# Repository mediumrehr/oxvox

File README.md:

# Ox Vox

The Ox Vox is a badge add-on created for the DEF CON 25 503 party and BSides PDX 2018 badges. The Ox Vox replaces the two joysticks on the badge with eight buttons and amplified speaker output.

## How To

### Connecting

Connecting the Ox Vox requires removing the joysticks from the badge. The pinouts are different for the DC25 Badge vs the BSides badge, so a few defines need to be changed depending on which badge you are modifying. Each joysticks uses five GPIOs, which allows for eight button inputs (a full octave), audio out, and an amplifier enable (see [Addition](#additions)).

Below shows how to connect the Ox Vox depending on which badge you're modifying.

#### DEF CON 25 503 Party Badge

#### BSides PDX Badge

### Programming

There are a few methods for programming the BMD-300 (NRF52832) SoC with the Ox Vox firmware via SWD. For this this project, I've been using the [BMD-300 Eval Kit](https://www.digikey.com/product-detail/en/rigado-inc/BMD-300-EVAL/1604-1007-ND/5958042) as a Segger J-Link Debugger as outlined in [this article](https://rigado.zendesk.com/hc/en-us/articles/223486428-How-are-the-BMD-200-and-BMD-300-Series-modules-programmed-). There are many cheap (<$10) J-Link-OB devices available that will likely work just as well, or you can probably use any other SWD device you have laying around.

In order to program the board, you need to break out the SWD interface. This requires soldering four male header pins to the pads shown below (directly below the i2c screen header). Looking at the badge from the back, the pins are SWCLK, SWDIO, 3v3, and GND.

If you're using a J-Link interface, the badge should show mount to your OS when you plug it into your computer. You can then drop the appropriate (DC25 vs BSides) compiled hex file into the mounted folder and the NRF52 will take it from there.

If you want to build from source, follow [this guide](https://www.rigado.com/bmd-300-series-getting-started-guide/?wpdmdl=1810) (starting on page 9) for setting up Keil uVision, the nRF5 SDK, and Segger J-Link. Instead of downloading nRF5 SDK v12, download [nRF5 SDK v13.0.0](https://developer.nordicsemi.com/nRF5_SDK/nRF5_SDK_v13.x.x/) (it's possible this code will work with newer SDKs, but I have not tested with them).

## Hardware

PCB files, designed in Eagle v7.7.0, are included in the Hardware folder. The design features eight momentary-push buttons, a basic smoothing and amplifier circuit, and a .8W speaker. The buttons form a full octave keyboard from C (261.6 Hz) to C (523.3 Hz). The BMD-300 outputs a PWM signal that is smoothed and amplified by the LM4861 amplifier.

## Firmware

To build the project, drop the oxvox foldering into examples->peripheral in the SDK and drop components into the root of the SDK (it fixes a bug in the bsp driver and adds the board definitions to the boards folder). Opening oxvox.uvprojx will open the project in uVision. From there you can build and load the hex file onto the board (either by grabbing the hex file in \_build/ and dropping it onto the mounted JLINK device or by using uVision's load feature). If you're using uVision to load the firmware, make sure it is configured to support whatever SWD programmer you are using; you can configure this under Project->Options for Target->Debug.

## Additions

The Ox Vox amplifier, in combination with the OLED display, were quickly draining fresh batteries, so as proposed by [Scanlime](https://twitter.com/scanlime), I added support in the firmware to connect the shutown pin of the LM4861 to pin xxx of the BMD-300. This allows the amplifier to be turned off when no audio is being played in order to save some power, and so it doesn't compete with the current draw when the display is drawing more white pixels in the default image. In order to do this, the shutdown lead (highlighted below) needs to be desoldered and lifted off the pad, then wired to the xxx pad on the Badge. The shutdown pin was originally connected to ground so the amplifier would remain on, therefore part of the trace is under the LM4861. The easiest way to break that connection is to lift the lead instead of disconnect the pad.

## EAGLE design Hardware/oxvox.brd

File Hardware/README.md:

### OX VOX Hardware
Schematic and layout created using [Eagle 7.7.0](https://www.autodesk.com/products/eagle/overview)

The design features eight momentary-push buttons, a basic smoothing and amplifier circuit, and a 800mW speaker. The buttons form a full octave keyboard from C (261.6 Hz) to C (523.3 Hz). The BMD-300 outputs a PWM signal that is smoothed and amplified by the LM4861 amplifier.

This layout is slightly different from the DC25 and BSidesPDX layouts. It features the LM4861 shutdown pin broken out, as suggested by [Micah Scott](https://github.com/scanlime). By breaking out the shutdown pin and connecting it to the remaining available BMD-300 GPIO, the amplifier can be to shutdown when not in use in order to save power. Please see the connection section for how to connect this, or connect it to ground to keep the amplifier always on.

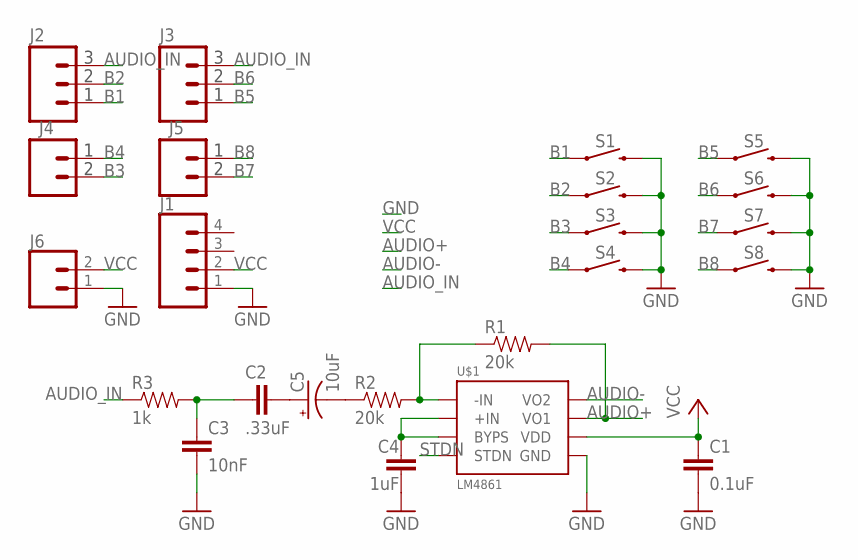
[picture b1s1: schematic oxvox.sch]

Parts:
C1: 0.1uF; 0603-CAP
C2: .33uF; 0603-CAP
C3: 10nF; 0603-CAP
C4: 1uF; 0603-CAP
C5: 10uF; RADIAL_SMT_4MM
J1: CONN_04; 1X04
J2, J3: M03-PTH_LONG_NO_SILK_BOT; M03_LONG_NO_SILK_BOTTOM
J4, J5: M02-PTH_LONG_NO_SILK_BOT; M02_LONG_NO_SILK_BOTTOM
J6: CONN_02; 1X02
R1, R2: 20k; 0805
R3: 1k; 0603-RES
S1, S2, S3, S4, S5, S6, S7, S8: MOMENTARY-SWITCH-SPST-PTH-6.0MM-KIT-ALL2; TACTILE_SWITCH_PTH_6.0MM_KIT_NOSILK
U$1: LM4861; 8-SOIC

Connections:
AUDIO+: R1.2, U$1.P$5 (VO1)
AUDIO-: U$1.P$8 (VO2)
AUDIO_IN: J2.P$3, J3.P$3, R3.1
B1: J2.P$1, S1.1, S1.2 (1)
B2: J2.P$2, S2.1, S2.2 (1)
B3: J4.P$2, S3.1, S3.2 (1)
B4: J4.P$1, S4.1, S4.2 (1)
B5: J3.P$1, S5.1, S5.2 (1)
B6: J3.P$2, S6.1, S6.2 (1)
B7: J5.P$2, S7.1, S7.2 (1)
B8: J5.P$1, S8.1, S8.2 (1)
GND: C1.2, C3.2, C4.2, J1.1, J6.1, S1.3 (2), S1.4 (2), S2.3 (2), S2.4 (2), S3.3 (2), S3.4 (2), S4.3 (2), S4.4 (2), S5.3 (2), S5.4 (2), S6.3 (2), S6.4 (2), S7.3 (2), S7.4 (2), S8.3 (2), S8.4 (2), U$1.P$7 (GND)
unnamed: R1.1, R2.2, U$1.P$4 (-IN)
unnamed: C2.2, C3.1, R3.2
unnamed: C5.P$2 (-), R2.1
unnamed: C4.1, U$1.P$2 (BYPS), U$1.P$3 (+IN)
unnamed: C2.1, C5.P$1 (+)
STDN: U$1.P$1 (STDN)
VCC: C1.1, J1.2, J6.2, U$1.P$6 (VDD)

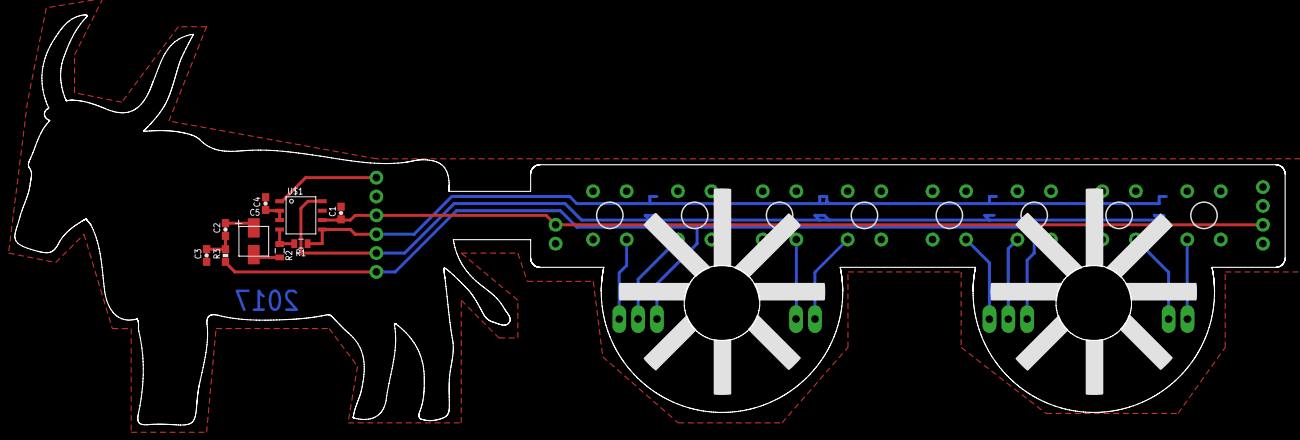
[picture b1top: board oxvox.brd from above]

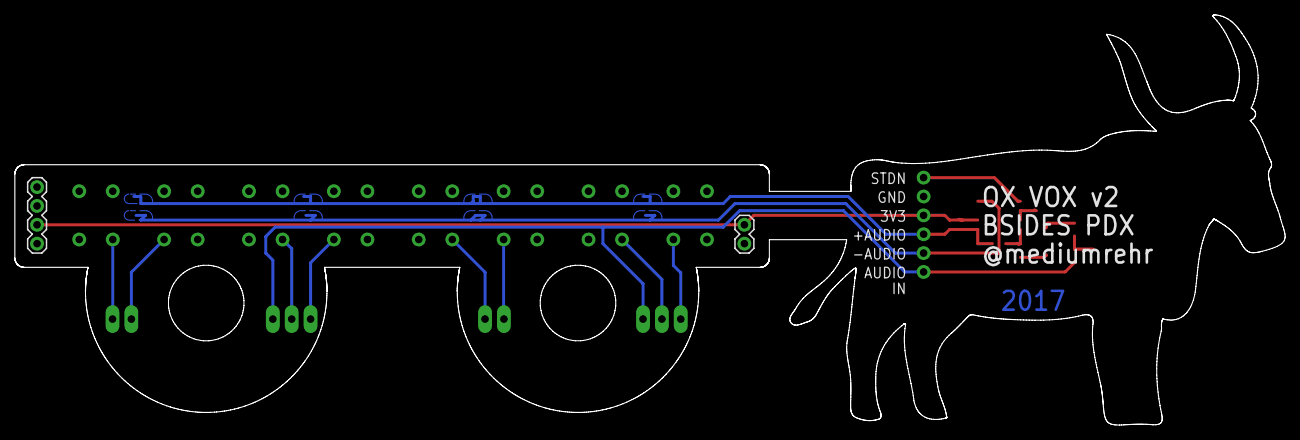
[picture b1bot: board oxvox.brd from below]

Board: 2 copper layers, 171.1 x 55.2 mm, 23 parts (6 on the bottom side), 17 nets.

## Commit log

2018-03-07 hardware files added
2018-03-28 initial firmware commit
2018-03-28 update readme with build instructions
2018-04-19 fix pinout configuration
2018-04-19 add diagrams to readme
2018-04-19 improve diagram size
2018-04-19 add script to convert bmp to array for display

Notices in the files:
parts and their libraries:
SparkFun-Passives: Licensing: Creative Commons ShareAlike 4.0 International - https://creativecommons.org/licenses/by-sa/4.0
